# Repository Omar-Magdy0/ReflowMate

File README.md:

# Reflow Mate

--- 

## Your open-source mate to PCB reflowing

#### Idea :
Your companion to pcb repair , assembly and testing , starting with Reflow capabilities...

To start small , grow big. current focus is mainly on providing :
* Digital Soldering iron support
* Hot air gun support
* 3d printable Accessories

#### Added :
* Hardware Core  (AC dimmers and related circuitry, DC Dimmer and related circuitry , Thermocouple interface , NTC interface , Expansion connectors)
#### Planned to be added :
* Fluid and mobile friendly web interface
* TFT LCD interface
* Modern and robust enclosure while keeping it small for mobility 

#### This project is a working in progress and still under testing and development

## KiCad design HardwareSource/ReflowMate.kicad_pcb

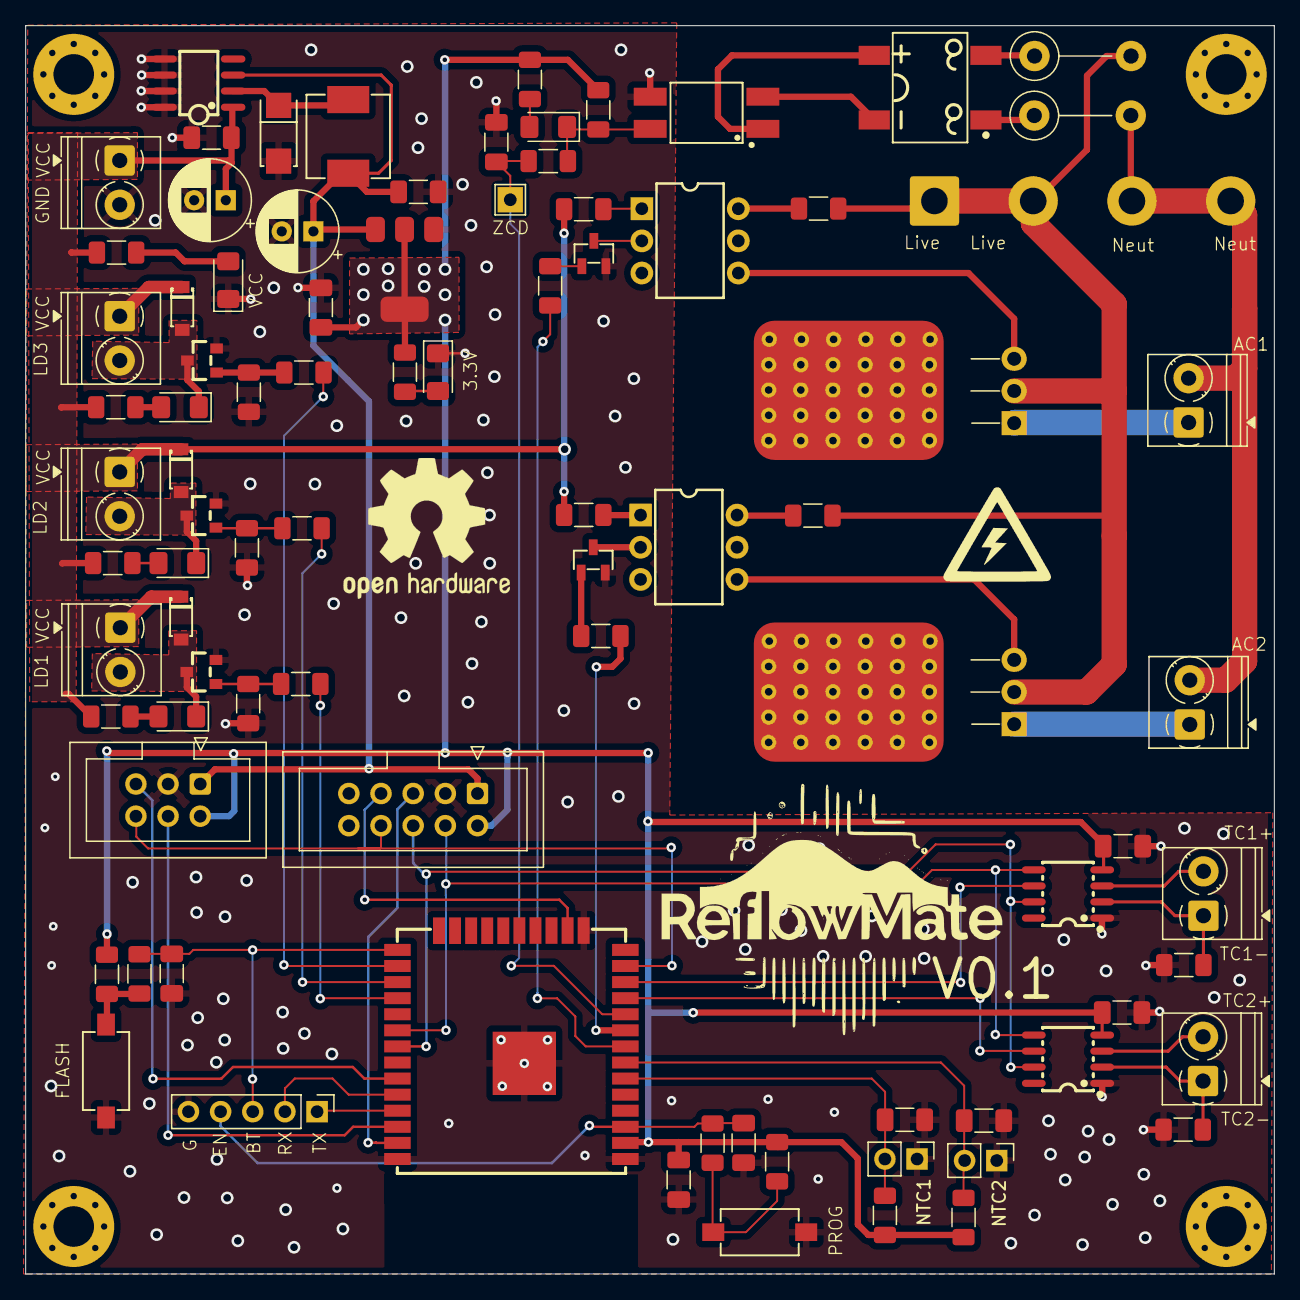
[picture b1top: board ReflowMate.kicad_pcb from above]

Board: 2 copper layers, 98.6 x 98.6 mm, 94 parts (1 on the bottom side), 63 nets.

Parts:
C1, C3, C5, C7: 1u-50V; C_1206_3216Metric_Pad1.33x1.80mm_HandSolder
C2, C4, C11, C12, C13: 100n; C_1206_3216Metric_Pad1.33x1.80mm_HandSolder
C6: 100uF-35V; CP_Radial_D6.3mm_P2.50mm
C8: 180uF-10V; CP_Radial_D6.3mm_P2.50mm
C9, C10: 10u; C_1206_3216Metric_Pad1.33x1.80mm_HandSolder
D1: SS34_C8678; SMA_L4.3-W2.6-LS5.2-RD
D2, D3: LED RED; LED_1206_3216Metric_Pad1.42x1.75mm_HandSolder
D4, D6, D8: SD103AW_C181204; SOD-123_L2.8-W1.8-LS3.7-RD
D5, D7, D9, D11: LED; LED_1206_3216Metric_Pad1.42x1.75mm_HandSolder
D10: DB107S_C525738; DBS_L8.4-W6.4-P5.10-LS10.2-BL
H1, H2, H3, H4: MountingHole_Pad; MountingHole_3.2mm_M3_Pad_Via
H6: Logo_Open_Hardware_Large; OSHW-Logo2_14.6x12mm_SilkScreen
HS1, HS2: Heatsink_Pad; TO-220 HeatPad
J1: Conn_01x05_Pin; PinHeader_1x05_P2.54mm_Vertical
J2: Conn_02x03_Counter_Clockwise; IDC-Header_2x03_P2.54mm_Vertical
J3: Conn_02x05_Counter_Clockwise; IDC-Header_2x05_P2.54mm_Vertical
J4, J6, J7, J8, J9, J10, J11, J12: Screw_Terminal_01x02; TerminalBlock_Phoenix_PT-1,5-2-3.5-H_1x02_P3.50mm_Horizontal
J5: Conn_01x04_Socket; SolderWire-1.5sqmm_1x04_P7.8mm_D1.7mm_OD3.9mm
J13: NTC1; PinHeader_1x02_P2.54mm_Vertical
J14: NTC2; PinHeader_1x02_P2.54mm_Vertical
L1: SMMS0650-680M; IND-SMD_L7.1-W6.6_H5.0
Q1, Q2: S9013_C402281; SOT-23-3_L2.9-W1.3-P0.95-LS2.4-BR
Q3, Q4: BT136-500; TO-220-3_Horizontal_TabDown
Q5, Q6, Q7: AO3400_C2938367; SOT-23_L2.9-W1.3-P1.90-LS2.4-BR
R1, R3, R7, R8, R14, R16, R17, R18, R20, R21, R25, R26: 10k; R_1206_3216Metric_Pad1.30x1.75mm_HandSolder
R2, R4, R5, R6, R9, R10: 1k; R_1206_3216Metric_Pad1.30x1.75mm_HandSolder
R11, R12: 360; R_1206_3216Metric_Pad1.30x1.75mm_HandSolder
R13, R15, R19, R27: 680; R_1206_3216Metric_Pad1.30x1.75mm_HandSolder
R22, R23: 33k (1W); R_Axial_DIN0411_L9.9mm_D3.6mm_P7.62mm_Vertical
R24, R28: 0; R_1206_3216Metric_Pad1.30x1.75mm_HandSolder
R29, R30: 4.7K; R_1206_3216Metric_Pad1.30x1.75mm_HandSolder
SW1, SW2: TSB008A2526A; SW-SMD_L6.0-W3.5-LS8.0
T1, T2: MOC3020M; DIP-6_L8.5-W6.4-P2.54-LS7.6-BL
TP1: ZCS_TP; TestPoint_THTPad_2.0x2.0mm_Drill1.0mm
U1: ESP32-WROOM-32D; WIFIM-SMD_39P-L25.5-W18.0-P1.27-BL
U2: XL1509-5.0E1; SOIC-8_L5.0-W4.0-P1.27-LS6.0-BL
U3: AMS1117-3.3; SOT-223-3_TabPin2_NOSILKSCREEN
U4, U6: MAX31855KASA+T; SO-8_L4.9-W3.9-P1.27-LS5.9-BL
U5: EL817S1C(F); SOP-4_L6.5-W4.6-P2.54-LS10.3-TL

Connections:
+3.3V: C1.1, C10.1, C11.2, C13.2, J2.2, J3.2, R1.2, R3.2, R6.1, R25.1, R26.2, R29.1, R30.1, U1.2 (VDD33), U3.2 (VO), U4.4 (VCC), U6.4 (VCC)
+5V: C8.1, C9.1, J2.1, J3.1, L1.2, U2.3 (FB), U3.3 (VI)
+24V: C6.1, C7.1, D4.1 (K), D6.1 (K), D8.1 (K), J4.1, J7.1, J11.1, J12.1, R5.1, R9.2, R10.2, R16.1, R18.1, R21.1, U2.1 (VIN)
/BOOT_MODE: C5.1, J1.3, R4.2, U1.25 (IO0)
/EN: C3.1, J1.4, R2.2, U1.3 (EN)
/I2C_SCL: J2.4, U1.36 (IO22)
/I2C_SDA: J2.5, U1.33 (IO21)
/PROG_RX: J1.2, U1.34 (RXD0)
/PROG_TX: J1.1, U1.35 (TXD0)
/SPI_CS0: J3.7, U1.16 (IO13)
/SPI_RST: J2.6, J3.8, U1.13 (IO14)
AcLoad1+: J10.1, Q4.1 (A1)
AcLoad1Control: R7.1, U1.8 (IO32)
AcLoad2+: J6.1, Q3.1 (A1)
AcLoad2Control: R8.1, U1.9 (IO33)
DC_Load1-: D4.2 (A), D5.1 (K), J11.2, Q5.3 (D)
DC_Load2-: D8.2 (A), D9.1 (K), J12.2, Q7.3 (D)
DC_Load3-: D6.2 (A), D7.1 (K), J7.2, Q6.3 (D)
DcControl1: R13.2, U1.28 (IO17)
DcControl2: R19.2, U1.27 (IO16)
DcControl3: R15.2, U1.26 (IO4)
GND: C1.2, C2.2, C3.2, C4.2, C5.2, C6.2, C7.2, C8.2, C9.2, C10.2, C11.1, C12.2, C13.1, D1.2 (A), D2.1 (K), D3.1 (K), J1.5, J2.3, J3.3, J4.2, J13.1, J14.1, Q1.2 (E), Q2.2 (E), Q5.2 (S), Q6.2 (S), Q7.2 (S), R14.2, R17.2, R20.2, R24.2, R28.2, SW1.1, SW2.1, U1.1 (GND), U1.15 (GND), U1.38 (GND), U1.39 (GND), U2.5 (GND), U2.6 (GND), U2.7 (GND), U2.8 (GND), U3.1 (GND), U4.1 (GND), U5.3, U6.1 (GND)
LINE: J5.1, J5.2, Q3.2 (A2), Q4.2 (A2), R11.1, R12.1, R22.2
NEUT: J5.3, J5.4, J6.2, J10.2, R23.2
NTC1: C2.1, J13.2, R29.2, U1.6 (IO34)
NTC2: C4.1, J14.2, R30.2, U1.7 (IO35)
unnamed: D1.1 (K), L1.1, U2.2 (OUTPUT)
unnamed: D2.2 (A), R5.2
unnamed: D3.2 (A), R6.2
unnamed: D5.2 (A), R16.2
unnamed: D7.2 (A), R18.2
unnamed: D9.2 (A), R21.2
unnamed: D10.3 (+), U5.1
unnamed: D10.4 (-), U5.2
unnamed: D10.1 (AC), R23.1
unnamed: D10.2 (AC), R22.1
unnamed: D11.2 (A), R25.2
unnamed: D11.1 (K), R26.1, R27.2, U5.4
unnamed: Q1.1 (B), R7.2
unnamed: Q1.3 (C), T2.2 (CAT)
unnamed: Q2.1 (B), R8.2
unnamed: Q2.3 (C), T1.2 (CAT)
unnamed: Q3.3 (G), T1.4 (MT)
unnamed: Q4.3 (G), T2.4 (MT)
unnamed: Q5.1 (G), R13.1, R14.1
unnamed: Q6.1 (G), R15.1, R17.1
unnamed: Q7.1 (G), R19.1, R20.1
unnamed: R1.1, R2.1, SW1.2
unnamed: R3.1, R4.1, SW2.2
unnamed: R11.2, T1.6 (MT)
unnamed: R12.2, T2.6 (MT)
unnamed: R10.1, T1.1 (AN)
unnamed: R9.1, T2.1 (AN)
SPI_CLK: J3.4, U1.30 (IO18), U4.5 (SCK), U6.5 (SCK)
SPI_CS1: U1.11 (IO26), U4.6 (~CS)
SPI_CS2: U1.12 (IO27), U6.6 (~CS)
SPI_MISO: J3.6, U1.31 (IO19), U4.7 (SO), U6.7 (SO)
SPI_MOSI: J3.5, U1.37 (IO23)
Termocouple1+: J8.2, U4.3 (T+)
Termocouple1-: J8.1, R24.1, U4.2 (T-)
Termocouple2+: J9.2, U6.3 (T+)
Termocouple2-: J9.1, R28.1, U6.2 (T-)
/ZCD: C12.1, R27.1, TP1.1, U1.10 (IO25)

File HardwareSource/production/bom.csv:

Designator,Footprint,Quantity,Value,LCSC Part #
"C1, C3, C5, C7",1206,4,1u-50V,C1848
"C10, C9",1206,2,10u,C7432781
"C11, C12, C13, C2, C4",1206,5,100n,C24497
D1,SMA_L4.3-W2.6-LS5.2-RD,1,SS34_C8678,C8678
D10,DBS_L8.4-W6.4-P5.10-LS10.2-BL,1,DB107S_C525738,C525738
"D11, D5, D7, D9",1206,4,LED,C965822
"D2, D3",1206,2,LED RED,C965822
"D4, D6, D8",SOD-123_L2.8-W1.8-LS3.7-RD,3,SD103AW_C181204,C181204
L1,IND-SMD_L7.1-W6.6_H5.0,1,SMMS0650-680M,C2894721
"Q1, Q2",SOT-23-3_L2.9-W1.3-P0.95-LS2.4-BR,2,S9013_C402281,C402281
"Q3, Q4",TO-220-3_Horizontal_TabDown,2,BT136-500,C916781
"Q5, Q6, Q7",SOT-23_L2.9-W1.3-P1.90-LS2.4-BR,3,AO3400_C2938367,C2938367
"R1, R14, R16, R17, R18, R20, R21, R25, R26, R3, R7, R8",1206,12,10k,C17902
"R10, R2, R4, R5, R6, R9",1206,6,1k,C2907440
"R11, R12",1206,2,360,C2907486
"R13, R15, R19, R27",1206,4,680,C2907528
"R22, R23",R_Axial_DIN0411_L9.9mm_D3.6mm_P7.62mm_Vertical,2,33k (1W),C20625284
"R24, R28",1206,2,0,C2907406
"R29, R30",1206,2,4.7K,C137262
"SW1, SW2",SW-SMD_L6.0-W3.5-LS8.0,2,TSB008A2526A,C2888456
"T1, T2",DIP-6_L8.5-W6.4-P2.54-LS7.6-BL,2,MOC3020M,C86911
U1,WIFIM-SMD_39P-L25.5-W18.0-P1.27-BL,1,ESP32-WROOM-32D,C473012
U2,SOIC-8_L5.0-W4.0-P1.27-LS6.0-BL,1,XL1509-5.0E1,C61063
U3,SOT-223-3_TabPin2_NOSILKSCREEN,1,AMS1117-3.3,C347222
"U4, U6",SO-8_L4.9-W3.9-P1.27-LS5.9-BL,2,MAX31855KASA+T,C52028
U5,SOP-4_L6.5-W4.6-P2.54-LS10.3-TL,1,EL817S1C(F),C2912100

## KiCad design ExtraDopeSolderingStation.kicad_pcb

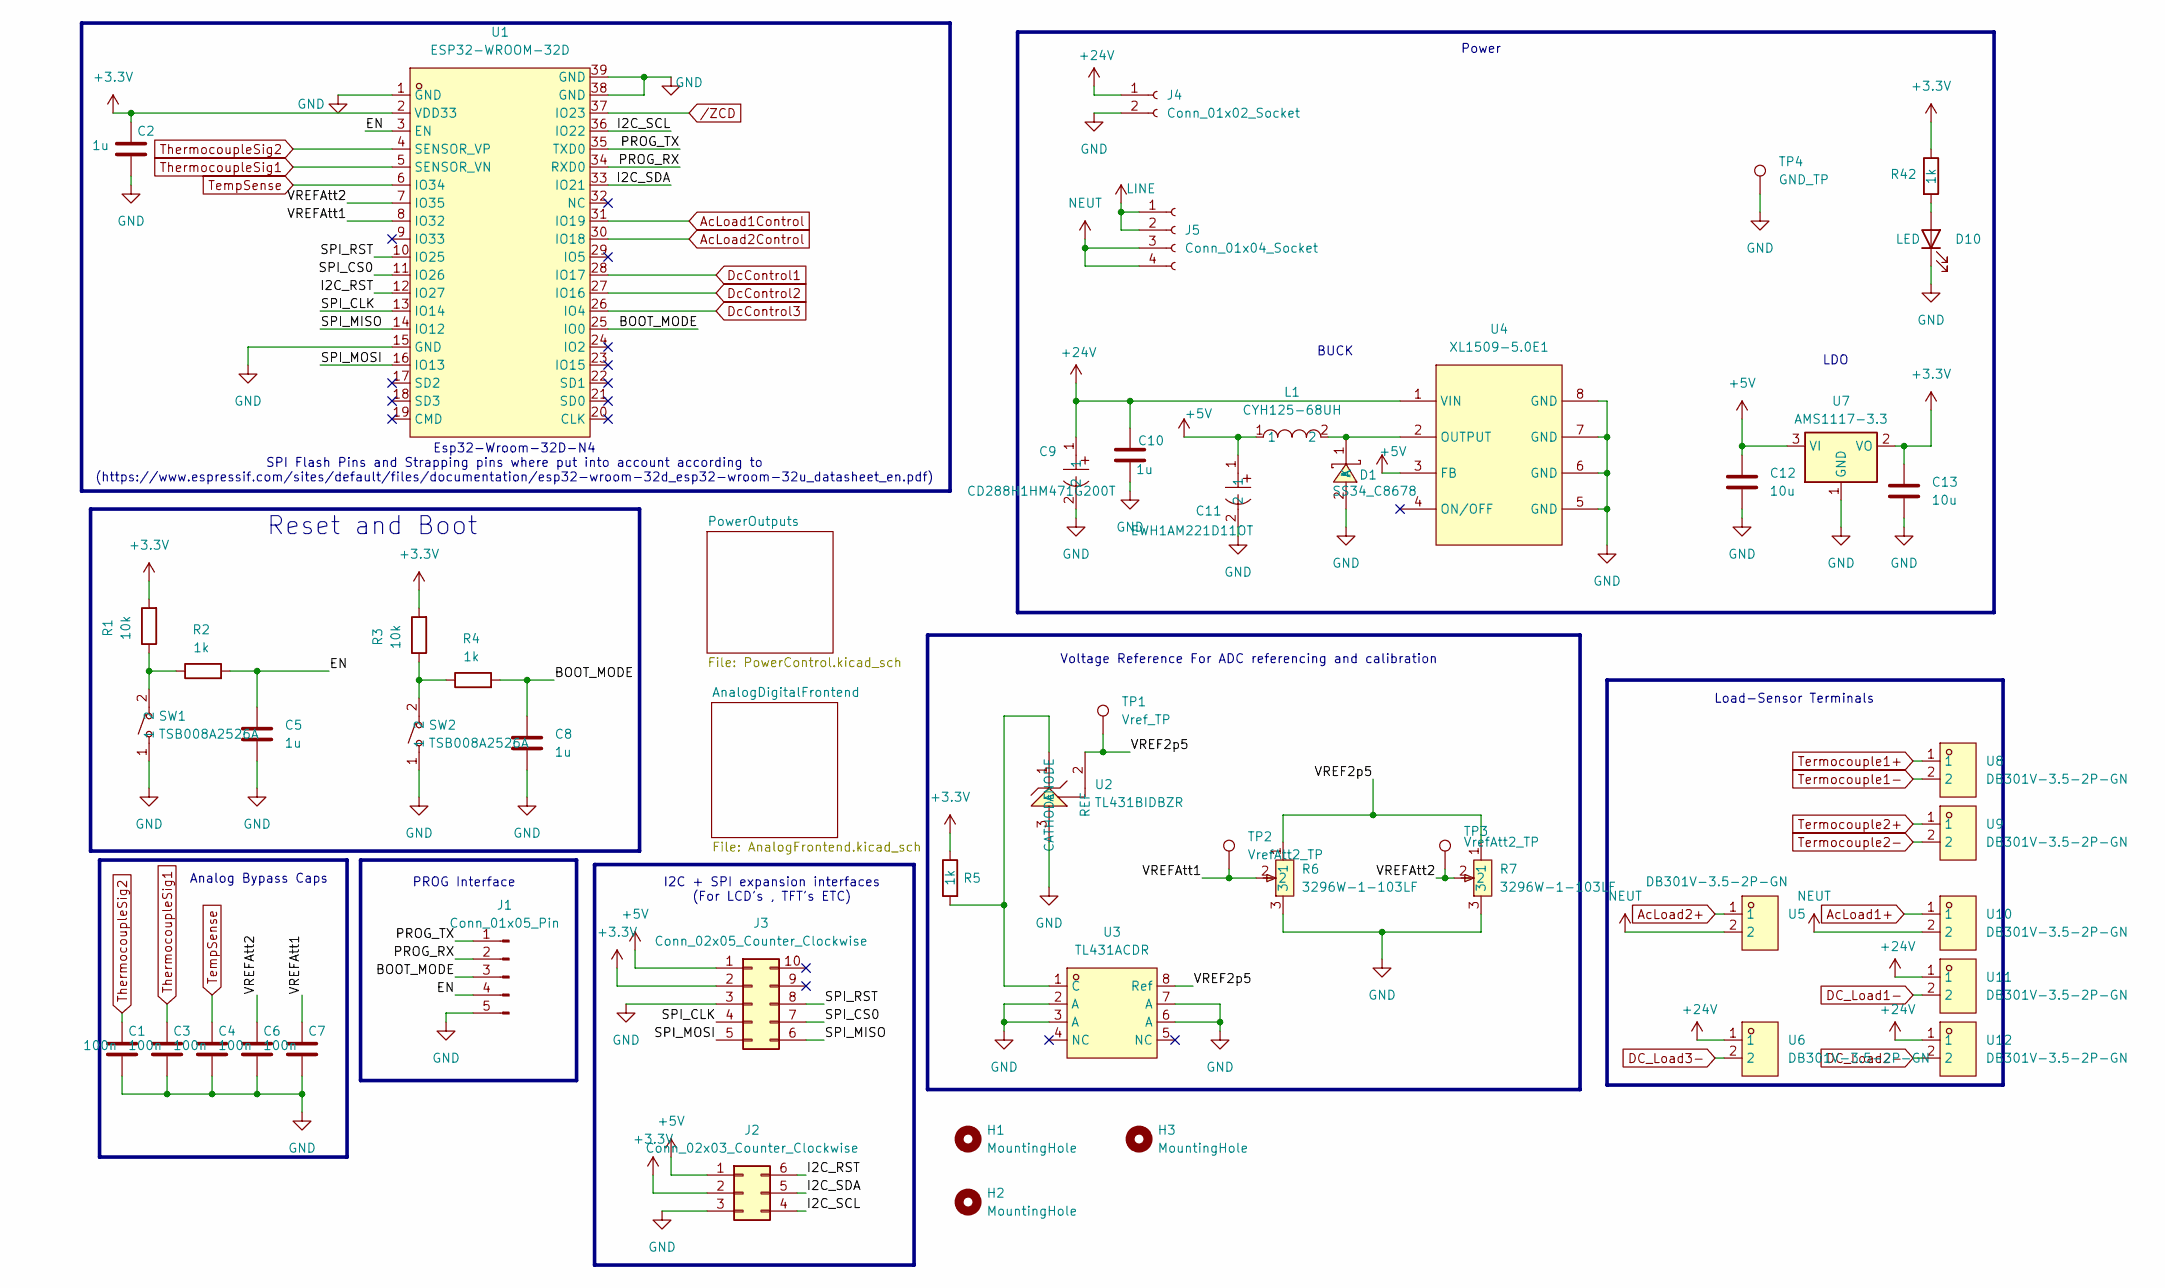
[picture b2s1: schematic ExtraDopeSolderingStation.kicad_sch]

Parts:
C1, C3, C4, C6, C7: 100n; C_1206_3216Metric_Pad1.33x1.80mm_HandSolder
C2, C5, C8, C10: 1u; C_1206_3216Metric_Pad1.33x1.80mm_HandSolder
C9: CD288H1HM471G200T; CAP-TH_BD10.0-P5.00-D0.6-FD; LCSC Part C42460494
C11: EWH1AM221D11OT; CAP-TH_BD5.0-P2.00-D0.5-FD-A; LCSC Part C2988873
C12, C13: 10u; C_1206_3216Metric_Pad1.33x1.80mm_HandSolder
D1: SS34_C8678; SMA_L4.3-W2.6-LS5.2-RD; LCSC Part C8678
D10: LED; LED_1206_3216Metric_Pad1.42x1.75mm_HandSolder
H1, H2, H3: MountingHole; MountingHole_3.2mm_M3_Pad_Via
J1: Conn_01x05_Pin; PinHeader_1x05_P2.54mm_Vertical
J2: Conn_02x03_Counter_Clockwise; IDC-Header_2x03_P2.54mm_Vertical
J3: Conn_02x05_Counter_Clockwise; IDC-Header_2x05_P2.54mm_Vertical
J4: Conn_01x02_Socket; SolderWire-0.5sqmm_1x02_P4.6mm_D0.9mm_OD2.1mm
J5: Conn_01x04_Socket; SolderWire-0.5sqmm_1x04_P4.6mm_D0.9mm_OD2.1mm
L1: CYH125-68UH; IND-SMD_L12.5-W12.5; LCSC Part C7431083
R1, R3: 10k; R_1206_3216Metric_Pad1.30x1.75mm_HandSolder
R2, R4, R5, R42: 1k; R_1206_3216Metric_Pad1.30x1.75mm_HandSolder
R6, R7: 3296W-1-103LF; RES-ADJ-TH_3296W; LCSC Part C34846
SW1, SW2: TSB008A2526A; SW-SMD_L6.0-W3.5-LS8.0; LCSC Part C2888456
TP1: Vref_TP; TestPoint_THTPad_2.0x2.0mm_Drill1.0mm
TP2, TP3: VrefAtt2_TP; TestPoint_THTPad_2.0x2.0mm_Drill1.0mm
TP4: GND_TP; TestPoint_THTPad_2.0x2.0mm_Drill1.0mm
U1: ESP32-WROOM-32D; WIFIM-SMD_39P-L25.5-W18.0-P1.27-BL; LCSC Part C473012
U2: TL431BIDBZR; SOT-23-3_L2.9-W1.3-P1.90-LS2.4-BR; LCSC Part C41283
U3: TL431ACDR; SOIC-8_L4.9-W3.9-P1.27-LS6.0-BL; LCSC Part C67475
U4: XL1509-5.0E1; SOIC-8_L5.0-W4.0-P1.27-LS6.0-BL; LCSC Part C61063
U5, U6, U8, U9, U10, U11, U12: DB301V-3.5-2P-GN; CONN-TH_DB301V-3.5-2P-GN; LCSC Part C695629
U7: AMS1117-3.3; SOT-223-3_TabPin2

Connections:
+3.3V: C2.1, C13.1, J2.2, J3.2, R1.2, R3.2, R5.1, R42.1, U1.2 (VDD33), U7.2 (VO); also elsewhere on the board
+5V: C11.1, C12.1, J2.1, J3.1, L1.1, U4.3 (FB), U7.3 (VI)
+24V: C9.1, C10.1, J4.1, U4.1 (VIN), U6.1, U11.1, U12.1; also elsewhere on the board
/BOOT_MODE: C8.1, J1.3, R4.2, U1.25 (IO0)
/EN: C5.1, J1.4, R2.2, U1.3 (EN)
/I2C_RST: J2.6, U1.12 (IO27)
/I2C_SCL: J2.4, U1.36 (IO22)
/I2C_SDA: J2.5, U1.33 (IO21)
/PROG_RX: J1.2, U1.34 (RXD0)
/PROG_TX: J1.1, U1.35 (TXD0)
/SPI_CLK: J3.4, U1.13 (IO14)
/SPI_CS0: J3.7, U1.11 (IO26)
/SPI_MISO: J3.6, U1.14 (IO12)
/SPI_MOSI: J3.5, U1.16 (IO13)
/SPI_RST: J3.8, U1.10 (IO25)
/VREF2p5: R6.1, R7.1, TP1.1, U2.2 (REF), U3.8 (Ref)
/VREFAtt1: C7.1, R6.2, TP2.1, U1.8 (IO32)
/VREFAtt2: C6.1, R7.2, TP3.1, U1.7 (IO35)
AcLoad1+: U10.1; also elsewhere on the board
AcLoad1Control: U1.31 (IO19); also elsewhere on the board
AcLoad2+: U5.1; also elsewhere on the board
AcLoad2Control: U1.30 (IO18); also elsewhere on the board
DC_Load1-: U11.2; also elsewhere on the board
DC_Load2-: U12.2; also elsewhere on the board
DC_Load3-: U6.2; also elsewhere on the board
DcControl1: U1.28 (IO17); also elsewhere on the board
DcControl2: U1.27 (IO16); also elsewhere on the board
DcControl3: U1.26 (IO4); also elsewhere on the board
GND: C1.2, C2.2, C3.2, C4.2, C5.2, C6.2, C7.2, C8.2, C9.2, C10.2, C11.2, C12.2, C13.2, D1.2 (A), D10.1 (K), J1.5, J2.3, J3.3, J4.2, R6.3, R7.3, SW1.1, SW2.1, TP4.1, U1.1 (GND), U1.15 (GND), U1.38 (GND), U1.39 (GND), U2.3 (ANODE), U3.2 (A), U3.3 (A), U3.6 (A), U3.7 (A), U4.5 (GND), U4.6 (GND), U4.7 (GND), U4.8 (GND), U7.1 (GND); also elsewhere on the board
LINE: J5.1, J5.2; also elsewhere on the board
NEUT: J5.3, J5.4, U5.2, U10.2; also elsewhere on the board
unnamed: D1.1 (K), L1.2, U4.2 (OUTPUT)
unnamed: D10.2 (A), R42.2
unnamed: R1.1, R2.1, SW1.2
unnamed: R3.1, R4.1, SW2.2
unnamed: R5.2, U2.1 (CATHODE), U3.1 (C)
TempSense: C4.1, U1.6 (IO34); also elsewhere on the board
Termocouple1+: U8.1; also elsewhere on the board
Termocouple1-: U8.2; also elsewhere on the board
Termocouple2+: U9.1; also elsewhere on the board
Termocouple2-: U9.2; also elsewhere on the board
ThermocoupleSig1: C3.1, U1.5 (SENSOR_VN); also elsewhere on the board
ThermocoupleSig2: C1.1, U1.4 (SENSOR_VP); also elsewhere on the board
/ZCD: U1.37 (IO23); also elsewhere on the board

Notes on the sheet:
Analog Bypass Caps
Esp32-Wroom-32D-N4 SPI Flash Pins and Strapping pins where put into account according to (https://www.espressif.com/sites/default/files/documentation/esp32-wroom-32d_esp32-wroom-32u_datasheet_en.pdf)
Power
Voltage Reference For ADC referencing and calibration
LDO
Load-Sensor Terminals
Reset and Boot
BUCK
I2C + SPI expansion interfaces (For LCD's , TFT's ETC)
PROG Interface

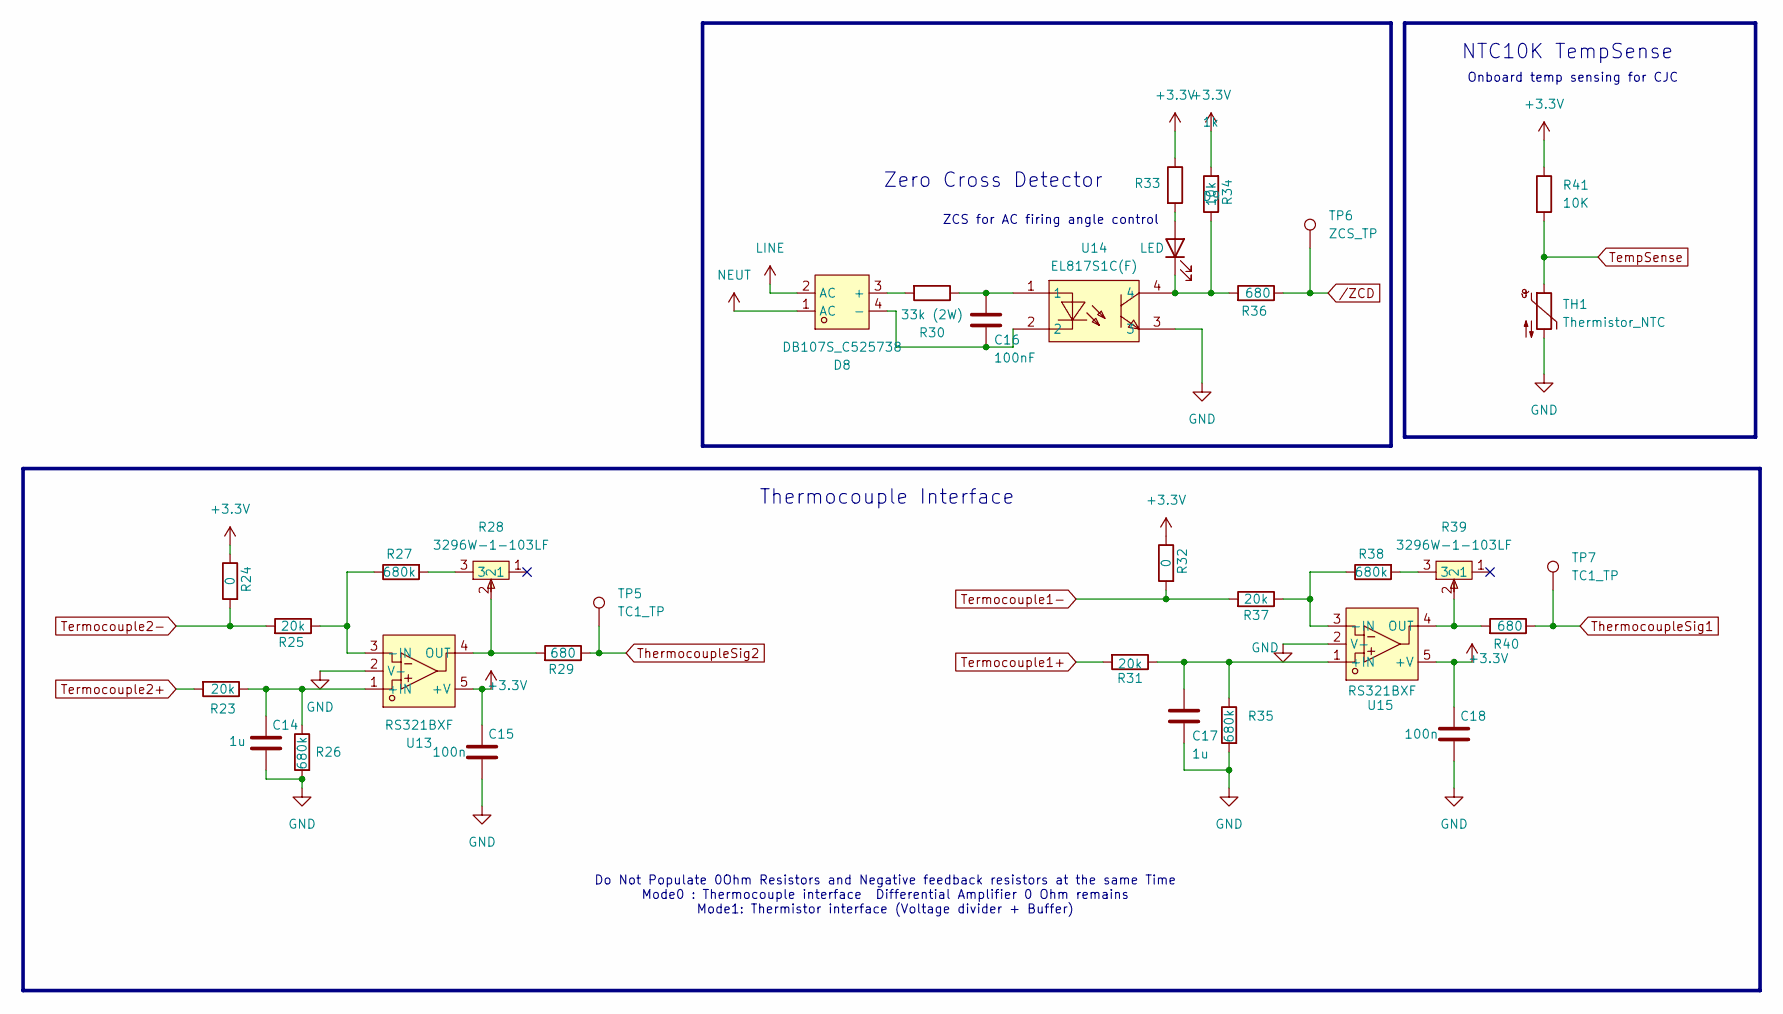
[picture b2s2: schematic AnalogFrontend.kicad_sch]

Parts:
C14, C17: 1u; C_1206_3216Metric_Pad1.33x1.80mm_HandSolder
C15, C18: 100n; C_1206_3216Metric_Pad1.33x1.80mm_HandSolder
C16: 100nF; C_1206_3216Metric_Pad1.33x1.80mm_HandSolder
D8: DB107S_C525738; DBS_L8.4-W6.4-P5.10-LS10.2-BL; LCSC Part C525738
D9: LED; LED_1206_3216Metric_Pad1.42x1.75mm_HandSolder
R23, R25, R31, R37: 20k; R_1206_3216Metric_Pad1.30x1.75mm_HandSolder
R24, R32: 0; R_1206_3216Metric_Pad1.30x1.75mm_HandSolder
R26, R27, R35, R38: 680k; R_1206_3216Metric_Pad1.30x1.75mm_HandSolder
R28, R39: 3296W-1-103LF; RES-ADJ-TH_3296W; LCSC Part C34846
R29, R36, R40: 680; R_1206_3216Metric_Pad1.30x1.75mm_HandSolder
R30: 33k (2W); R_Axial_DIN0414_L11.9mm_D4.5mm_P15.24mm_Horizontal
R33: 1k; R_1206_3216Metric_Pad1.30x1.75mm_HandSolder
R34: 10k; R_1206_3216Metric_Pad1.30x1.75mm_HandSolder
R41: 10K; R_1206_3216Metric_Pad1.30x1.75mm_HandSolder
TH1: Thermistor_NTC; R_Axial_DIN0207_L6.3mm_D2.5mm_P2.54mm_Vertical
TP5, TP7: TC1_TP; TestPoint_THTPad_2.0x2.0mm_Drill1.0mm
TP6: ZCS_TP; TestPoint_THTPad_2.0x2.0mm_Drill1.0mm
U13, U15: RS321BXF; SOT-23-5_L2.9-W1.6-P0.95-LS2.8-BL; LCSC Part C237022
U14: EL817S1C(F); SOP-4_L6.5-W4.6-P2.54-LS10.3-TL; LCSC Part C2912100

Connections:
+3.3V: C15.1, C18.1, R24.1, R32.1, R33.1, R34.2, R41.1, U13.5 (+V), U15.5 (+V); also elsewhere on the board
GND: C14.2, C15.2, C17.2, C18.2, R26.2, R35.2, TH1.2, U13.2 (V-), U14.3, U15.2 (V-); also elsewhere on the board
LINE: D8.2 (AC); also elsewhere on the board
NEUT: D8.1 (AC); also elsewhere on the board
unnamed: C16.1, R30.1, U14.1
unnamed: D8.3 (+), R30.2
unnamed: C16.2, D8.4 (-), U14.2
unnamed: D9.2 (A), R33.2
unnamed: D9.1 (K), R34.1, R36.2, U14.4
unnamed: R27.2, R28.3
unnamed: R38.2, R39.3
unnamed: C14.1, R23.1, R26.1, U13.1 (+IN)
unnamed: R25.1, R27.1, U13.3 (-IN)
unnamed: R28.2, R29.2, U13.4 (OUT)
unnamed: C17.1, R31.1, R35.1, U15.1 (+IN)
unnamed: R37.1, R38.1, U15.3 (-IN)
unnamed: R39.2, R40.2, U15.4 (OUT)
TempSense: R41.2, TH1.1; also elsewhere on the board
Termocouple1+: R31.2; also elsewhere on the board
Termocouple1-: R32.2, R37.2; also elsewhere on the board
Termocouple2+: R23.2; also elsewhere on the board
Termocouple2-: R24.2, R25.2; also elsewhere on the board
ThermocoupleSig1: R40.1, TP7.1; also elsewhere on the board
ThermocoupleSig2: R29.1, TP5.1; also elsewhere on the board
/ZCD: R36.1, TP6.1; also elsewhere on the board

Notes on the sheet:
Zero Cross Detector
Do Not Populate 0Ohm Resistors and Negative feedback resistors at the same Time Mode0 : Thermocouple interface Differential Amplifier 0 Ohm remains Mode1: Thermistor interface (Voltage divider + Buffer)
Thermocouple Interface
NTC10K TempSense
ZCS for AC firing angle control
Onboard temp sensing for CJC

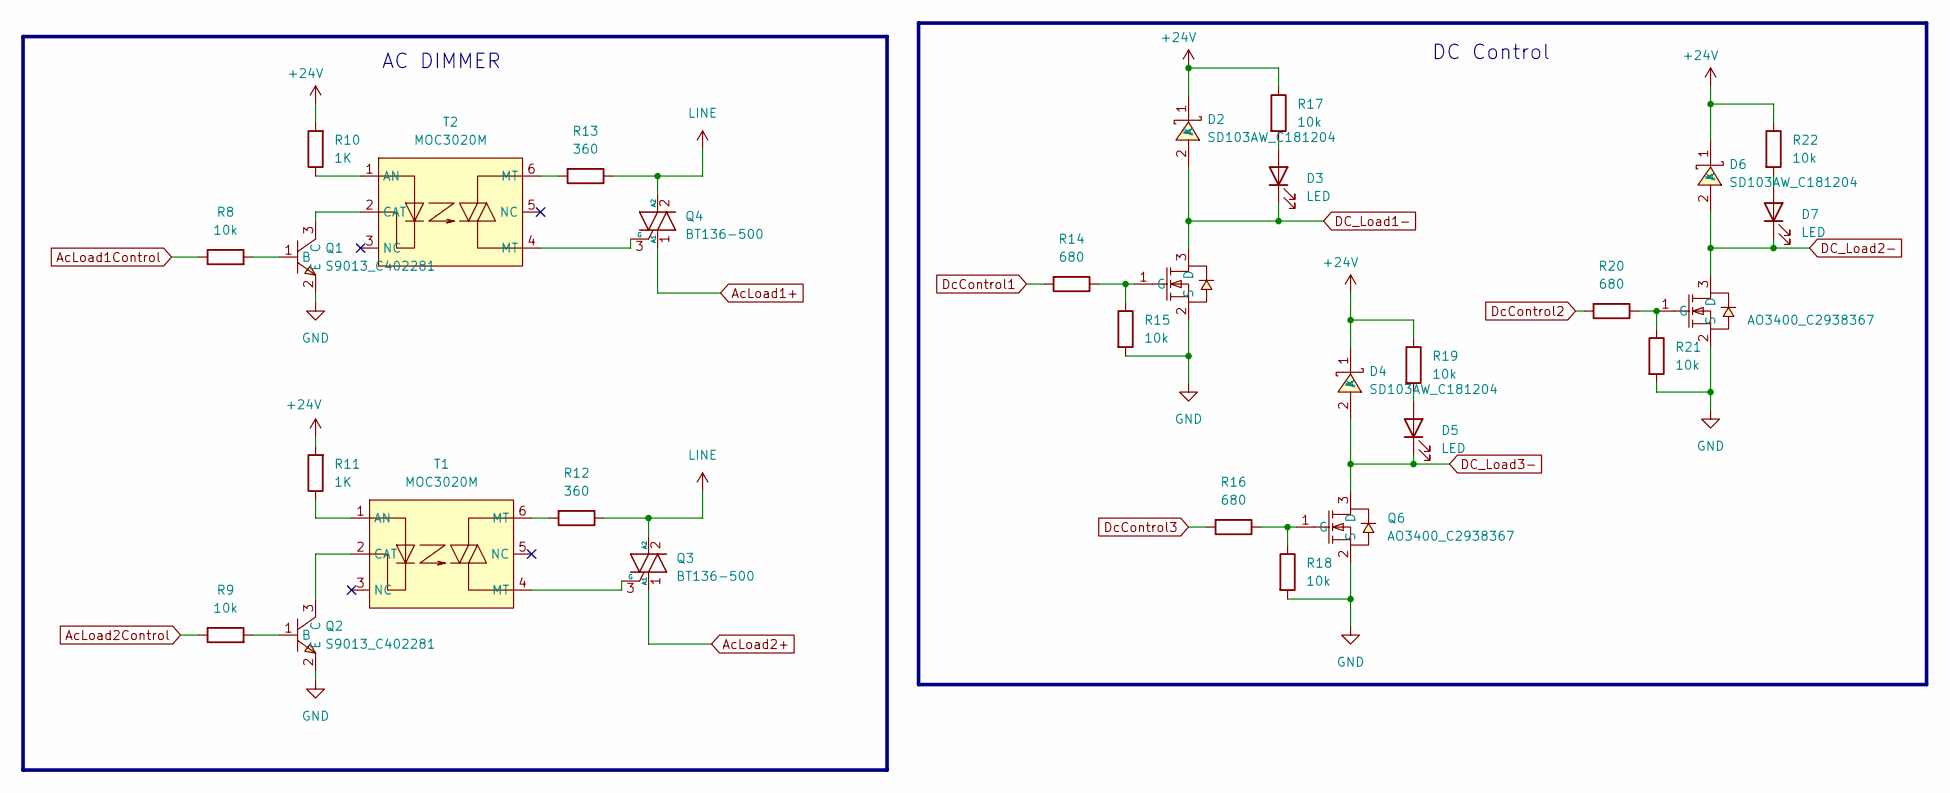
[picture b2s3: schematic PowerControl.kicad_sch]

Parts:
D2, D4, D6: SD103AW_C181204; SOD-123_L2.8-W1.8-LS3.7-RD; LCSC Part C181204
D3, D5, D7: LED; LED_1206_3216Metric_Pad1.42x1.75mm_HandSolder
Q1, Q2: S9013_C402281; SOT-23-3_L2.9-W1.3-P0.95-LS2.4-BR; LCSC Part C402281
Q3, Q4: BT136-500; TO-220-3_Horizontal_TabDown
Q5, Q6, Q7: AO3400_C2938367; SOT-23_L2.9-W1.3-P1.90-LS2.4-BR; LCSC Part C2938367
R8, R9, R15, R17, R18, R19, R21, R22: 10k; R_1206_3216Metric_Pad1.30x1.75mm_HandSolder
R10, R11: 1K; R_1206_3216Metric_Pad1.30x1.75mm_HandSolder
R12, R13: 360; R_1206_3216Metric_Pad1.30x1.75mm_HandSolder
R14, R16, R20: 680; R_1206_3216Metric_Pad1.30x1.75mm_HandSolder
T1, T2: MOC3020M; DIP-6_L8.5-W6.4-P2.54-LS7.6-BL; LCSC Part C86911

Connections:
+24V: D2.1 (K), D4.1 (K), D6.1 (K), R10.2, R11.2, R17.1, R19.1, R22.1; also elsewhere on the board
AcLoad1+: Q4.1 (A1); also elsewhere on the board
AcLoad1Control: R8.1; also elsewhere on the board
AcLoad2+: Q3.1 (A1); also elsewhere on the board
AcLoad2Control: R9.1; also elsewhere on the board
DC_Load1-: D2.2 (A), D3.1 (K), Q5.3 (D); also elsewhere on the board
DC_Load2-: D6.2 (A), D7.1 (K), Q7.3 (D); also elsewhere on the board
DC_Load3-: D4.2 (A), D5.1 (K), Q6.3 (D); also elsewhere on the board
DcControl1: R14.2; also elsewhere on the board
DcControl2: R20.2; also elsewhere on the board
DcControl3: R16.2; also elsewhere on the board
GND: Q1.2 (E), Q2.2 (E), Q5.2 (S), Q6.2 (S), Q7.2 (S), R15.2, R18.2, R21.2; also elsewhere on the board
LINE: Q3.2 (A2), Q4.2 (A2), R12.1, R13.1; also elsewhere on the board
unnamed: D3.2 (A), R17.2
unnamed: D5.2 (A), R19.2
unnamed: D7.2 (A), R22.2
unnamed: Q1.1 (B), R8.2
unnamed: Q1.3 (C), T2.2 (CAT)
unnamed: Q2.1 (B), R9.2
unnamed: Q2.3 (C), T1.2 (CAT)
unnamed: Q3.3 (G), T1.4 (MT)
unnamed: Q4.3 (G), T2.4 (MT)
unnamed: Q5.1 (G), R14.1, R15.1
unnamed: Q6.1 (G), R16.1, R18.1
unnamed: Q7.1 (G), R20.1, R21.1
unnamed: R12.2, T1.6 (MT)
unnamed: R13.2, T2.6 (MT)
unnamed: R11.1, T1.1 (AN)
unnamed: R10.1, T2.1 (AN)

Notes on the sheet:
DC Control
AC DIMMER

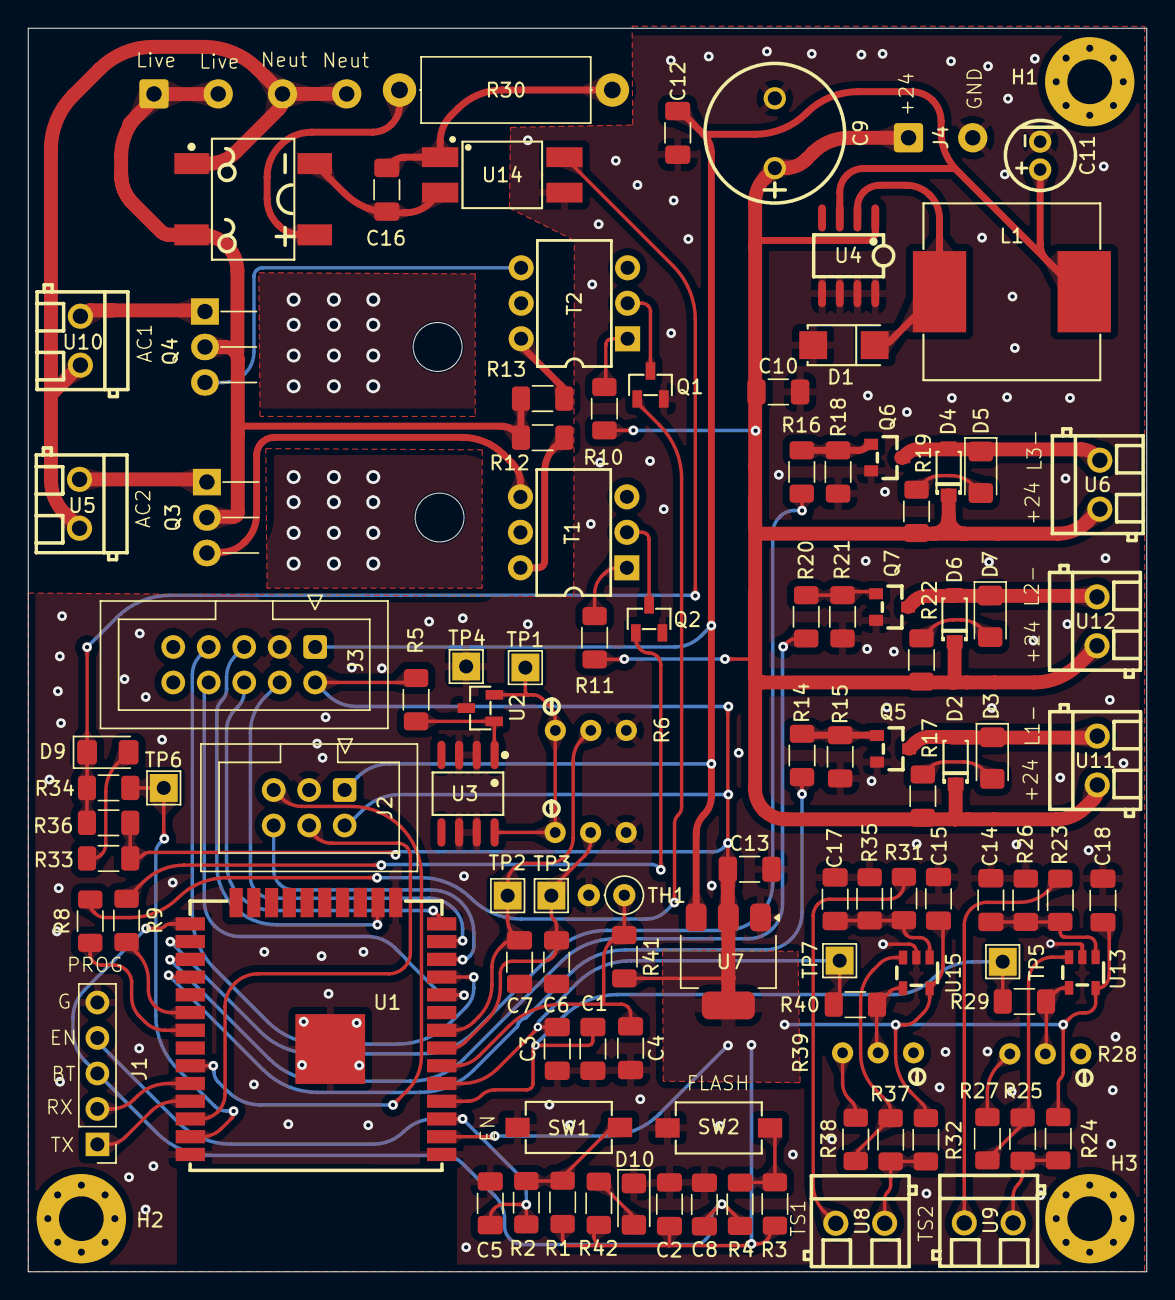
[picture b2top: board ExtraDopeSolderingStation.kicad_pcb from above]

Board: 2 copper layers, 80.1 x 89.0 mm, 113 parts (1 on the bottom side), 73 nets.

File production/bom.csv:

Designator,Footprint,Quantity,Value,LCSC Part #
"C1, C15, C18, C3, C4, C6, C7",1206,7,100n,
"C10, C14, C17, C2, C5, C8",1206,6,1u,
C11,CAP-TH_BD5.0-P2.00-D0.5-FD-A,1,EWH1AM221D11OT,C2988873
"C12, C13",1206,2,10u,
C16,1206,1,100nF,
C9,CAP-TH_BD10.0-P5.00-D0.6-FD,1,CD288H1HM471G200T,C42460494
D1,SMA_L4.3-W2.6-LS5.2-RD,1,SS34_C8678,C8678
"D10, D3, D5, D7, D9",1206,5,LED,
"D2, D4, D6",SOD-123_L2.8-W1.8-LS3.7-RD,3,SD103AW_C181204,C181204
D8,DBS_L8.4-W6.4-P5.10-LS10.2-BL,1,DB107S_C525738,C525738
J1,PinHeader_1x05_P2.54mm_Vertical,1,Conn_01x05_Pin,
J2,IDC-Header_2x03_P2.54mm_Vertical,1,Conn_02x03_Counter_Clockwise,
J3,IDC-Header_2x05_P2.54mm_Vertical,1,Conn_02x05_Counter_Clockwise,
J4,SolderWire-0.5sqmm_1x02_P4.6mm_D0.9mm_OD2.1mm,1,Conn_01x02_Socket,
J5,SolderWire-0.5sqmm_1x04_P4.6mm_D0.9mm_OD2.1mm,1,Conn_01x04_Socket,
L1,IND-SMD_L12.5-W12.5,1,CYH125-68UH,C7431083
"Q1, Q2",SOT-23-3_L2.9-W1.3-P0.95-LS2.4-BR,2,S9013_C402281,C402281
"Q3, Q4",TO-220-3_Horizontal_TabDown,2,BT136-500,
"Q5, Q6, Q7",SOT-23_L2.9-W1.3-P1.90-LS2.4-BR,3,AO3400_C2938367,C2938367
"R1, R15, R17, R18, R19, R21, R22, R3, R34, R41, R8, R9",1206,12,10k,
"R10, R11, R2, R33, R4, R42, R5",1206,7,1K,
"R12, R13",1206,2,360,
"R14, R16, R20, R29, R36, R40",1206,6,680,
"R23, R25, R31, R37",1206,4,20k,
"R24, R32",1206,2,0,
"R26, R27, R35, R38",1206,4,680k,
"R28, R39, R6, R7",RES-ADJ-TH_3296W,4,3296W-1-103LF,C34846
R30,R_Axial_DIN0414_L11.9mm_D4.5mm_P15.24mm_Horizontal,1,33k (2W),
"SW1, SW2",SW-SMD_L6.0-W3.5-LS8.0,2,TSB008A2526A,C2888456
"T1, T2",DIP-6_L8.5-W6.4-P2.54-LS7.6-BL,2,MOC3020M,C86911
TH1,R_Axial_DIN0207_L6.3mm_D2.5mm_P2.54mm_Vertical,1,Thermistor_NTC,
TP1,TestPoint_THTPad_2.0x2.0mm_Drill1.0mm,1,Vref_TP,
"TP2, TP3",TestPoint_THTPad_2.0x2.0mm_Drill1.0mm,2,VrefAtt2_TP,
TP4,TestPoint_THTPad_2.0x2.0mm_Drill1.0mm,1,GND_TP,
"TP5, TP7",TestPoint_THTPad_2.0x2.0mm_Drill1.0mm,2,TC1_TP,
TP6,TestPoint_THTPad_2.0x2.0mm_Drill1.0mm,1,ZCS_TP,
U1,WIFIM-SMD_39P-L25.5-W18.0-P1.27-BL,1,ESP32-WROOM-32D,C473012
"U10, U11, U12, U5, U6, U8, U9",CONN-TH_DB301V-3.5-2P-GN,7,DB301V-3.5-2P-GN,C695629
"U13, U15",SOT-23-5_L2.9-W1.6-P0.95-LS2.8-BL,2,RS321BXF,C237022
U14,SOP-4_L6.5-W4.6-P2.54-LS10.3-TL,1,EL817S1C(F),C2912100
U2,SOT-23-3_L2.9-W1.3-P1.90-LS2.4-BR,1,TL431BIDBZR,C41283
U3,SOIC-8_L4.9-W3.9-P1.27-LS6.0-BL,1,TL431ACDR,C67475
U4,SOIC-8_L5.0-W4.0-P1.27-LS6.0-BL,1,XL1509-5.0E1,C61063
U7,SOT-223-3_TabPin2,1,AMS1117-3.3,

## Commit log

2025-08-01 ExtraDopeSolderingStationSchematic
2025-08-03 Finished Routing, Finished Schematic
    Yet to add , solderMask
2025-08-04 Fixed Silkscreen, Added production files
2025-09-18 Key Fixes and upgrade to V0.1
    Design reliance on dedicated thermocouple interface chip instead of calibrating adc and differential amplifier ; Neater routing ; Logos ; High voltage spacing for AC part
2025-09-18 ReadMe , Reorder Repo
